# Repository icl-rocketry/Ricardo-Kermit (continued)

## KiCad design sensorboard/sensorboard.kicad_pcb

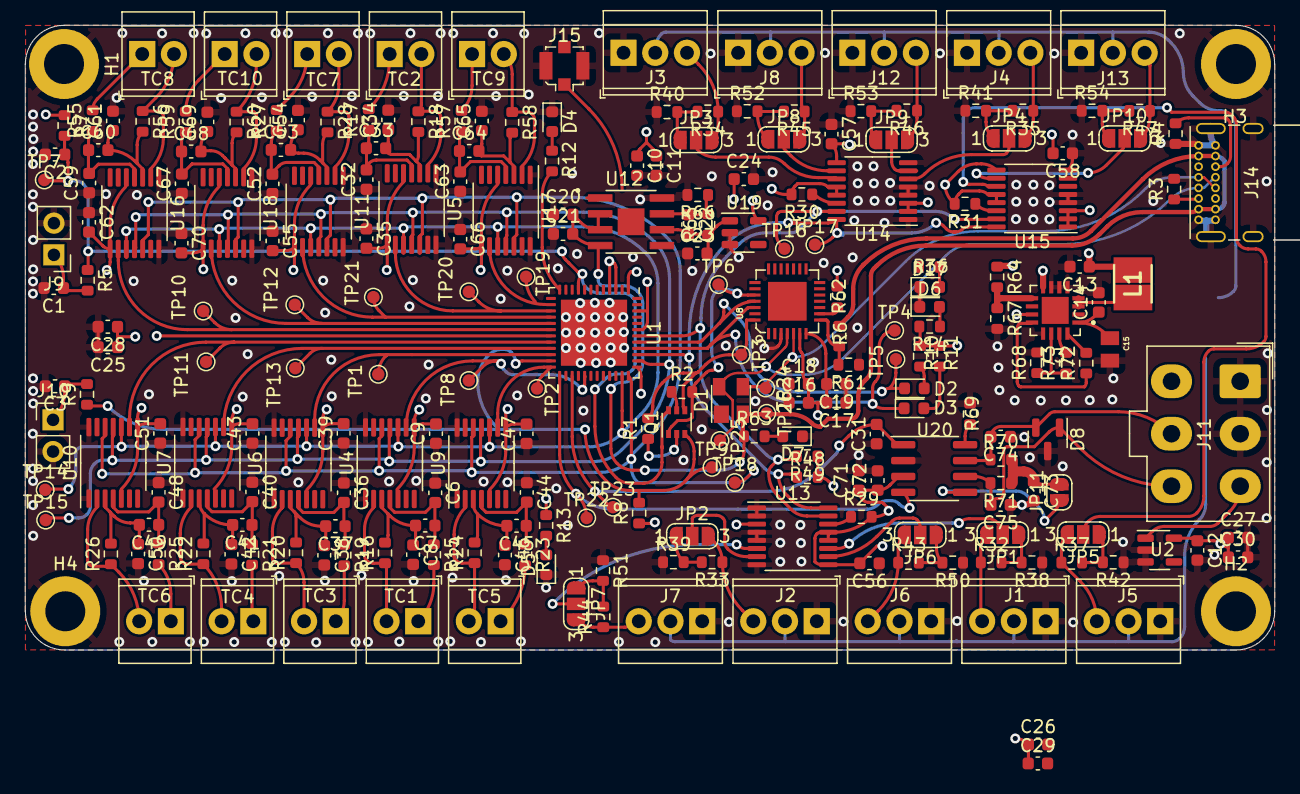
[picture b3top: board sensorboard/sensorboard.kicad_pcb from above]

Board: 4 copper layers, 100.0 x 50.0 mm, 243 parts (0 on the bottom side), 131 nets.

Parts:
C1, C2, C3, C21: 1uF; C_0603_1608Metric
C6, C8, C32, C34, C36, C38, C40, C42, C44, C46, C48, C50, C52, C54, C59, C61, C63, C65, C67, C69: 0.01uF; C_0603_1608Metric
C7, C9, C18, C19, C22, C33, C35, C37, C39, C41, C43, C45, C47, C49, C51, C53, C55, C56, C57, C58, C60, C62, C64, C66, C68, C70, C73: 0.1uF; C_0603_1608Metric
C10, C13, C20, C23, C25, C26, C27, C72: 10uF; C_0603_1608Metric
C11, C28, C29, C30, C71: 100nF; C_0603_1608Metric
C12, C16, C24: 4.7uF; C_0603_1608Metric
C14: 2.2uF; C_0603_1608Metric
C15: 100uF; CAPC2012X145N
C17: 1.0uF; C_0603_1608Metric
C31: 160pF; C_0603_1608Metric
C74: 220pF; C_0603_1608Metric
C75: 220 pF; C_0603_1608Metric
D1: SP0503BAHT; SOT-143
D2: RX_LED; LED_0603_1608Metric
D3: TX_LED; LED_0603_1608Metric
D4, D5: LED; LED_0603_1608Metric
D6: PWR_LED; LED_0603_1608Metric
D7, D17: USB_LED; LED_0603_1608Metric
D8: SM712_SOT23; SOT-23
H1, H2, H3, H4: MountingHole_Pad; MountingHole_3.2mm_M3_DIN965_Pad
J1, J2, J3, J4, J5, J6, J7, J8, J12, J13: Conn_01x03; TerminalBlock_TE_282834-3_1x03_P2.54mm_Horizontal
J9, J10: Conn_01x02_Male; PinHeader_1x02_P2.54mm_Vertical
J11: Conn_01x05_Male; Molex_Mini-Fit_Jr_5566-06A_2x03_P4.20mm_Vertical
J14: USB_C_Receptacle_USB2.0; USB_C_Receptacle_GCT_USB4085
J15: Conn_Coaxial; U.FL_Molex_MCRF_73412-0110_Vertical
JP1, JP2, JP3, JP4, JP5, JP6, JP7, JP8, JP9, JP10: SolderJumper_3_Open; SolderJumper-3_P1.3mm_Open_RoundedPad1.0x1.5mm_NumberLabels
JP11: SolderJumper_2_Open; SolderJumper-2_P1.3mm_Open_RoundedPad1.0x1.5mm
L1: 6.8uH; INDPM3030X200N
Q1: MMDT2222A; SOT-363_SC-70-6
R1, R2, R7, R8: 10K; R_0603_1608Metric
R3, R4: 5.1k; R_0603_1608Metric
R5, R9, R10, R11, R12, R13, R14, R36, R63: 470; R_0603_1608Metric
R6: 24k; R_0603_1608Metric
R15, R16, R17, R18, R19, R20, R21, R22, R23, R24, R25, R26, R27, R28, R55, R56, R57, R58, R59, R60: 100; R_0603_1608Metric
R29, R30, R31, R48, R49: 1k; R_0603_1608Metric
R32, R33, R34, R35, R37, R43, R44, R45, R46, R47: 22k; R_0603_1608Metric
R38, R39, R40, R41, R42, R50, R51, R52, R53, R54: 43k; R_0603_1608Metric
R61: 47k; R_0603_1608Metric
R62: 4.7k; R_0603_1608Metric
R64: 2.184M; R_0603_1608Metric
R65: 56k; R_0603_1608Metric
R66, R69: 10k; R_0603_1608Metric
R67: 390k; R_0603_1608Metric
R68: 200k; R_0603_1608Metric
R70, R71: 60; R_0603_1608Metric
R72: 1M; R_0603_1608Metric
R73: 1.8M; R_0603_1608Metric
TC1, TC2, TC3, TC4, TC5, TC6, TC7, TC8, TC9, TC10: Thermocouple; TerminalBlock_TE_282834-2_1x02_P2.54mm_Horizontal
TP1, TP2, TP3, TP4, TP5, TP6, TP7, TP8, TP9, TP10, TP11, TP12, TP13, TP14, TP15, TP16, TP17, TP18, TP19, TP20, TP21, TP22, TP23, TP24, TP25, TP26: TestPoint; TestPoint_Pad_D1.0mm
U1: ESP32-PICO-D4; QFN-48-1EP_7x7mm_P0.5mm_EP5.3x5.3mm
U2, U19: LTC4411; SOT-23-5
U3: TPS61092RSAR; QFN65P400X400X100-17N
U4, U5, U6, U7, U9, U10, U11, U16, U17, U18: MAX31856; TSSOP-14_4.4x5mm_P0.65mm
U8: CP2102-GMR-QFN28; QFN28G_0.5-5X5MM
U12: SC2416H; SOIC127P599X175-9N
U13, U14, U15: ADS1219; TSSOP-16_4.4x5mm_P0.65mm
U20: SN65HVD230; SOIC-8_3.9x4.9mm_P1.27mm

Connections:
+3V3: C9.2, C10.1, C11.1, C12.1, C13.1, C16.2, C17.2, C18.2, C19.2, C24.1, C25.1, C26.1, C27.1, C28.1, C29.1, C30.1, C35.2, C39.2, C43.2, C47.2, C51.2, C55.2, C56.2, C57.2, C58.2, C62.2, C66.2, C70.2, C71.1, C72.1, L1.1, R7.1, R8.1, R10.1, R11.1, R13.1, R14.2, R29.2, R30.2, R31.2, R48.2, R49.1, R62.1, R64.1, U1.1 (VDDA), U1.3 (VDDA3P3), U1.4 (VDDA3P3), U1.19 (VDD3P3_RTC), U1.37 (VDD3P3_CPU), U1.43 (VDDA), U1.46 (VDDA), U2.5 (OUT), U3.8 (VBAT), U3.11 (EN), U4.5 (AVDD), U4.8 (DVDD), U5.5 (AVDD), U5.8 (DVDD), U6.5 (AVDD), U6.8 (DVDD), U7.5 (AVDD), U7.8 (DVDD), U8.6 (VDD), U8.7 (REGIN), U9.5 (AVDD), U9.8 (DVDD), U10.5 (AVDD), U10.8 (DVDD), U11.5 (AVDD), U11.8 (DVDD), U13.3 (~RESET), U13.9 (REFP), U13.12 (AVDD), U13.13 (DVDD), U14.2 (A1), U14.3 (~RESET), U14.9 (REFP), U14.12 (AVDD), U14.13 (DVDD), U15.1 (A0), U15.2 (A1), U15.3 (~RESET), U15.9 (REFP), U15.12 (AVDD), U15.13 (DVDD), U16.5 (AVDD), U16.8 (DVDD), U17.5 (AVDD), U17.8 (DVDD), U18.5 (AVDD), U18.8 (DVDD), U19.5 (OUT), U20.3 (VCC)
+5V: C14.1, C15.1, J1.2, J2.2, J3.2, J4.2, J5.2, J6.2, J7.2, J8.2, J12.2, J13.2, R72.2, R73.2, U3.1 (VOUT), U3.15 (VOUT), U3.16 (VOUT)
/BOOT: Q1.3 (C2), R8.2, R9.1, TP9.1, U1.23 (IO0)
/CAN/Vref: JP11.1 (A), U20.5 (Vref)
/CAN_HIGH: C74.2, D8.2 (A2), J11.5, R70.1, U20.7 (CANH)
/CAN_LOW: C75.2, D8.1 (A1), J11.6, R71.2, U20.6 (CANL)
/CAN_RX: TP22.1, U1.25 (IO16), U20.4 (R)
/CAN_TX: C31.2, TP23.1, U1.27 (IO17), U20.1 (D)
/CS0: TP8.1, U1.29 (SD3/IO10), U4.9 (~CS)
/CS1: TP20.1, U1.15 (IO26), U5.9 (~CS)
/CS2: TP2.1, U1.24 (IO4), U9.9 (~CS)
/CS3: TP1.1, U1.22 (IO2), U6.9 (~CS)
/CS4: TP13.1, U1.21 (IO15), U7.9 (~CS)
/CS5: TP11.1, U1.20 (IO13), U10.9 (~CS)
/CS6: TP21.1, U1.16 (IO27), U11.9 (~CS)
/CS7: TP10.1, U1.18 (IO12), U16.9 (~CS)
/CS8: TP19.1, U1.14 (IO25), U17.9 (~CS)
/CS9: TP12.1, U1.17 (IO14), U18.9 (~CS)
/DTR: Q1.4 (E2), R1.2, TP3.1, U8.28 (DTR)
/EN: C2.1, Q1.6 (C1), R5.1, R7.2, TP7.1, U1.9 (EN)
/LED: R12.1, U1.12 (IO32)
/LNA_IN: J15.1 (In), U1.2 (LNA_IN)
/MISO: TP15.1, U1.38 (IO19), U4.11 (SDO), U5.11 (SDO), U6.11 (SDO), U7.11 (SDO), U9.11 (SDO), U10.11 (SDO), U11.11 (SDO), U16.11 (SDO), U17.11 (SDO), U18.11 (SDO)
/MOSI: TP18.1, U1.36 (IO23), U4.12 (SDI), U5.12 (SDI), U6.12 (SDI), U7.12 (SDI), U9.12 (SDI), U10.12 (SDI), U11.12 (SDI), U16.12 (SDI), U17.12 (SDI), U18.12 (SDI)
/RTS: Q1.1 (E1), R2.2, TP6.1, U8.24 (RTS)
/RXD: D2.1 (K), TP5.1, U1.41 (U0TXD/IO1), U8.25 (RXD)
/SCL: R48.1, TP17.1, U1.39 (IO22), U13.16 (SCL), U14.16 (SCL), U15.16 (SCL)
/SCLK: TP14.1, U1.35 (IO18), U4.10 (SCK), U5.10 (SCK), U6.10 (SCK), U7.10 (SCK), U9.10 (SCK), U10.10 (SCK), U11.10 (SCK), U16.10 (SCK), U17.10 (SCK), U18.10 (SCK)
/SDA: R49.2, TP16.1, U1.42 (IO21), U13.15 (SDA), U14.15 (SDA), U15.15 (SDA)
/TXD: D3.1 (K), TP4.1, U1.40 (U0RXD/IO3), U8.26 (TXD)
/analogueI2C/AIN0: JP1.2 (C), U13.11 (AIN0)
/analogueI2C/AIN1: JP6.2 (C), U13.10 (AIN1)
/analogueI2C/AIN2: JP2.2 (C), U13.7 (AIN2)
/analogueI2C/AIN3: JP7.2 (C), U13.6 (AIN3)
/analogueI2C/AIN4: JP3.2 (C), U14.11 (AIN0)
/analogueI2C/AIN5: JP8.2 (C), U14.10 (AIN1)
/analogueI2C/AIN6: JP4.2 (C), U14.6 (AIN3)
/analogueI2C/AIN7: JP9.2 (C), U14.7 (AIN2)
/analogueI2C/AIN8: JP5.2 (C), U15.11 (AIN0)
/analogueI2C/AIN9: JP10.2 (C), U15.10 (AIN1)
/usb/Data+: D1.4 (K), J14.A6 (D+), J14.B6 (D+), TP25.1, U8.4 (D+)
/usb/Data-: D1.3 (K), J14.A7 (D-), J14.B7 (D-), TP24.1, U8.5 (D-)
GND: C1.2, C2.2, C3.2, C6.1, C8.2, C9.1, C10.2, C11.2, C12.2, C13.2, C14.2, C15.2, C16.1, C17.1, C18.1, C19.1, C20.1, C21.1, C23.1, C24.2, C25.2, C26.2, C27.2, C28.2, C29.2, C30.2, C31.1, C32.1, C34.2, C35.1, C36.1, C38.2, C39.1, C40.1, C42.2, C43.1, C44.1, C46.2, C47.1, C48.1, C50.2, C51.1, C52.1, C54.2, C55.1, C56.1, C57.1, C58.1, C59.1, C61.2, C62.1, C63.1, C65.2, C66.1, C67.1, C69.2, C70.1, C71.2, C72.2, C73.2, C74.1, C75.1, D1.1 (A), D4.1 (K), D5.1 (K), D6.1 (K), D7.1 (K), D8.3 (common), D17.1 (K), H1.1, H2.1, H3.1, H4.1, J1.1, J2.1, J3.1, J4.1, J5.1, J6.1, J7.1, J8.1, J9.2, J10.2, J11.1, J11.2, J12.1, J13.1, J14.A1 (GND), J14.A12 (GND), J14.B1 (GND), J14.B12 (GND), J14.S1 (SHIELD), J15.2 (Ext), R3.2, R4.1, R38.1, R39.1, R40.1, R41.1, R42.1, R50.1, R51.1, R52.1, R53.1, R54.1, R61.1, R66.2, R67.2, R68.2, R69.2, U1.49 (GND), U2.2 (GND), U2.3 (CTL), U3.5 (PGND), U3.6 (PGND), U3.7 (PGND), U3.10 (SYNC), U3.13 (GND), U3.17 (PGND), U4.1 (AGND), U4.14 (DGND), U5.1 (AGND), U5.14 (DGND), U6.1 (AGND), U6.14 (DGND), U7.1 (AGND), U7.14 (DGND), U8.3 (GND), U9.1 (AGND), U9.14 (DGND), U10.1 (AGND), U10.14 (DGND), U11.1 (AGND), U11.14 (DGND), U12.8 (GND), U13.1 (A0), U13.2 (A1), U13.4 (DGND), U13.5 (AGND), U13.8 (REFN), U14.1 (A0), U14.4 (DGND), U14.5 (AGND), U14.8 (REFN), U15.4 (DGND), U15.5 (AGND), U15.8 (REFN), U16.1 (AGND), U16.14 (DGND), U17.1 (AGND), U17.14 (DGND), U18.1 (AGND), U18.14 (DGND), U19.2 (GND), U19.3 (CTL), U20.2 (GND)
unnamed: C1.1, J9.1, R5.2
unnamed: C3.1, J10.1, R9.2
unnamed: C6.2, C7.1, R15.1, U4.4 (T+)
unnamed: C7.2, C8.1, R16.2, U4.3 (T-)
unnamed: C23.2, R65.1, U12.6 (VOUT), U19.1 (IN)
unnamed: C32.2, C33.1, R17.1, U5.4 (T+)
unnamed: C33.2, C34.1, R18.2, U5.3 (T-)
unnamed: C36.2, C37.1, R19.1, U6.4 (T+)
unnamed: C37.2, C38.1, R20.2, U6.3 (T-)
unnamed: C40.2, C41.1, R21.1, U7.4 (T+)
unnamed: C41.2, C42.1, R22.2, U7.3 (T-)
unnamed: C44.2, C45.1, R23.1, U9.4 (T+)
unnamed: C45.2, C46.1, R24.2, U9.3 (T-)
unnamed: C48.2, C49.1, R25.1, U10.4 (T+)
unnamed: C49.2, C50.1, R26.2, U10.3 (T-)
unnamed: C52.2, C53.1, R27.1, U11.4 (T+)
unnamed: C53.2, C54.1, R28.2, U11.3 (T-)
unnamed: C59.2, C60.1, R55.1, U16.4 (T+)
unnamed: C60.2, C61.1, R56.2, U16.3 (T-)
unnamed: C63.2, C64.1, R57.1, U17.4 (T+)
unnamed: C64.2, C65.1, R58.2, U17.3 (T-)
unnamed: C67.2, C68.1, R59.1, U18.4 (T+)
unnamed: C68.2, C69.1, R60.2, U18.3 (T-)
unnamed: C73.1, JP11.2 (B), R70.2, R71.1
unnamed: D2.2 (A), R10.2
unnamed: D3.2 (A), R11.2
unnamed: D4.2 (A), R12.2
unnamed: D5.2 (A), R13.2
unnamed: D6.2 (A), R14.1
unnamed: D7.2 (A), R63.2
unnamed: D17.2 (A), R36.2
unnamed: J1.3, JP1.3 (B), R32.1
unnamed: J2.3, JP2.3 (B), R33.1
unnamed: J3.3, JP3.3 (B), R34.1
unnamed: J4.3, JP4.3 (B), R35.1
unnamed: J5.3, JP5.3 (B), R37.1
unnamed: J6.3, JP6.3 (B), R43.1
unnamed: J7.3, JP7.3 (B), R44.1
unnamed: J8.3, JP8.3 (B), R45.1
unnamed: J11.3, U2.1 (IN)
unnamed: J12.3, JP9.3 (B), R46.1
unnamed: J13.3, JP10.3 (B), R47.1
unnamed: J14.A5 (CC1), R3.1
unnamed: J14.B5 (CC2), R4.2
unnamed: JP1.1 (A), R32.2, R38.2
unnamed: JP2.1 (A), R33.2, R39.2
unnamed: JP3.1 (A), R34.2, R40.2
unnamed: JP4.1 (A), R35.2, R41.2
unnamed: JP5.1 (A), R37.2, R42.2
unnamed: JP6.1 (A), R43.2, R50.2
unnamed: JP7.1 (A), R44.2, R51.2
unnamed: JP8.1 (A), R45.2, R52.2
unnamed: JP9.1 (A), R46.2, R53.2
unnamed: JP10.1 (A), R47.2, R54.2
unnamed: L1.2, U3.3 (SW), U3.4 (SW)
unnamed: Q1.2 (B1), R1.1
unnamed: Q1.5 (B2), R2.1
unnamed: R6.2, R61.2, U8.8 (VBUS)
unnamed: R15.2, TC1.1 (+)
unnamed: R16.1, TC1.2 (-), U4.2 (BIAS)
unnamed: R17.2, TC2.1 (+)
unnamed: R18.1, TC2.2 (-), U5.2 (BIAS)
unnamed: R19.2, TC3.1 (+)
unnamed: R20.1, TC3.2 (-), U6.2 (BIAS)
unnamed: R21.2, TC4.1 (+)
unnamed: R22.1, TC4.2 (-), U7.2 (BIAS)
unnamed: R23.2, TC5.1 (+)
unnamed: R24.1, TC5.2 (-), U9.2 (BIAS)
unnamed: R25.2, TC6.1 (+)
unnamed: R26.1, TC6.2 (-), U10.2 (BIAS)
unnamed: R27.2, TC7.1 (+)
unnamed: R28.1, TC7.2 (-), U11.2 (BIAS)
unnamed: R29.1, U13.14 (~DRDY)
unnamed: R30.1, U14.14 (~DRDY)
unnamed: R31.1, U15.14 (~DRDY)
unnamed: R55.2, TC8.1 (+)
unnamed: R56.1, TC8.2 (-), U16.2 (BIAS)
unnamed: R57.2, TC9.1 (+)
unnamed: R58.1, TC9.2 (-), U17.2 (BIAS)
unnamed: R59.2, TC10.1 (+)
unnamed: R60.1, TC10.2 (-), U18.2 (BIAS)
unnamed: R62.2, U8.9 (~RST)
unnamed: R64.2, R67.1, U3.9 (LBI)
unnamed: R65.2, R66.1, U12.7 (ADJ)
unnamed: R68.1, R73.1, U3.14 (FB)
unnamed: R69.1, U20.8 (Rs)
unnamed: R72.1, U3.12 (LBO)
VBUS: C20.2, C21.2, D1.2 (K), J14.A4 (VBUS), J14.A9 (VBUS), J14.B4 (VBUS), J14.B9 (VBUS), R6.1, R63.1, TP26.1, U12.2 (EN), U12.3 (VIN)

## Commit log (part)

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2021-11-08 Initial sensor board schematic
    Laid out initial sensor board schematic for up to 12 ch inputs with 250Hz max sampling rate (at maximum oversampling rate of 16384) on continuous sampling mode
2021-11-09 Voltage divider setup
    Voltage divider setup, removed unused components, CAN RX/TX empty for now (waiting for kiran)
2021-11-09 Minor edits
    descriptors
2021-11-13 I2C ADC conversion+MCP31856 x10
    As above xD
    just need to do the pcb layout
2021-11-24 Antenna
2021-12-04 Small edits
    removed a floating extra antenna
2022-03-29 added 5v boost to schematic, should be ready for layout
2022-03-29 schemtiac update
2022-04-05 usb-uart structure done
    Original FPs were used, copies from usb were deleted, however the structure was kept the same
2022-04-13 CAN structure done
    Main structure copied across from actuator board, fps from sensor board used
2022-04-15 antenna and thermocouple prelim
    Preliminary layout for thermocouples and antenna structure done
2022-04-16 Changed diode fps from castellated
2022-05-21 Thermocouple structures
2022-05-31 Update thermocouple connection
    changed schematic (c55 --> cs5) and positions. Copies made
2022-06-03 thermocouple tps and connection update
2022-06-07 Integrated in USB and CAN
    CAN_TX and CAN_RX are moved
2022-06-07 3.3V connections and I2C capacitors
2022-06-11 moved the U14 component and added component
2022-06-18 transistor integration
2022-06-18 connectors and changed capacitor values
    capacitors for the connectors to 0.1uf
2022-06-18 rearrange CAN, USB port and new copies
2022-06-25 LEDs and repositioning for 5V
2022-06-27 Decoupling capacitors
2022-06-27 Initial GND fill and fixed CAN_HIGH
2022-07-02 fills and connecting islands
2022-07-03 Swapped the antenna for the coaxial connector
2022-07-13 USB moved, changed layer ln.2 to 3.3V
    Fixed the GND fill
2022-07-13 Change 3.3V, added curved edges
    changed the copy, added keepout for UFL connector
2022-07-13 changed BOOT pin, auto reset caps
    moved references about
2022-07-24 rearranged CAN and boost converter
    LEDs moved
2022-07-24 fixed clearance issues
    clearance set to 0.21mm
2022-07-26 boost converter fixed
    rearrangement of coaxial connector line and gnd stitching
2022-07-27 Changed pins for CAN lines and removed LED
    need to rearrange LNA_IN line for less interference
2022-07-27 added silkscreens and fixed LNA_IN line
    fixed labels for TPs and LEDs
2022-07-28 Solder jumper silkscreens and moved MOSI
2022-07-30 fixed CS lines
    before cleanup
2022-08-04 Connected LDO and CP2102 EPs to GND, expanded U.FL keepout
2022-08-12 folder structure, added ADS1219 code
2022-08-18 Changed default conversion mode from single-shot to continuous
2022-09-01 Added pin defs, shamelessly stolen .ini and partition files
    also moved ADS class and added the code I used to test 1 ADC channel
2022-09-05 Added config file, copied Ricardo_OS
2022-09-06 added submodules, deleted unnecessaryRic-OS files
2022-09-09 Copied ric-gateway,added getOffset and readAdjusted methods to ADS class
2022-09-18 offset calibration code fixed, found offsets for 1 of the sensor boards
2022-09-18 forgot to commit these
2022-09-19 fixed the ADS class
2022-09-23 Added NTC Thermistor class, tweaks to ADS class
2022-09-24 added pressure transducer class, explicitly cast all integers by length
2022-10-01 copied Kiran's e-match netconf, unfinished loadcell code
2022-10-05 Finished (maybe) loadcell class
2022-10-06 Added a telemetry command and a struct for analong sensors
    command numbers and stuff needs changing to integrate with the rest of the network
2022-10-07 changed telemetry command
2022-10-08 andrei use initializer lists
2022-10-08 updated librnp & rrc, fixed loadcell class
2022-10-08 Changed thermistor and ptap classes to use references instead of ptr
2022-10-08 added command to return raw adc readings
2022-10-08 Updated ADS class to use enums for data rates
2022-10-09 Defined random code numbers as static constexpr
2022-10-14 fixed ptaps and thermistor, load cell needs calibration
2022-10-21 EUROC fixes (I don't remember what I changed)
2022-11-05 Add pickle SD card + delete copies
    need to finish IO
2022-11-05 SD hierarchical labels
    need to connect to new GPIO for esp32-s3
2022-11-08 integrated new ESP32-s3
    Need to remove excess thermocouples
2022-11-08 removed thermocouples
    updated connections
2022-11-19 connectors and update
2022-11-22 potential divider preliminary
    for connectors
2022-12-06 values for ADC caps and connector circuits
    ADC cap values based on assumptions
2022-12-06 fixed hierarchical labels and added ref values
2022-12-10 added 10V rail, moved to boosts sheet
2022-12-13 update
    still need to fix 10v rail
2023-01-21 update 10v rail
2023-01-24 added template changes
    Moved power to seperate file
2023-01-28 grouping layout
2023-01-31 nanofit placements
2023-02-04 added low pass filters for ADC inputs
2023-02-04 update before power layout
2023-02-04 power layout done
2023-02-07 update (tps and filters)
2023-02-11 redimensioning to 120x50mm
    also finished tps
2023-02-21 10v rail layout, adc update
2023-02-21 ADC update
2023-02-25 esp32 pin rearrangement
2023-02-28 esp32-s3 placement
2023-02-28 ADC SPI connections
2023-03-04 ADC connections and KiCAD version update
2023-03-04 added LEDS and CAN connections
2023-03-11 changed pins layout for esp
    update for ADC traces
2023-03-11 traces for CAN and SD card done
2023-03-14 added values for the 10V option
2023-03-18 Powerlines and LDO layout
    updated fp for usb
2023-03-18 fix usb lines
2023-03-25 GND and 3.3v planes
2023-03-25 fixed planes and added tps
2023-03-25 Deleted thermal relief on mounting
2023-03-25 update
    not sure, forgot to save
2023-04-01 started writing zeroing stuff, pre-Romania commit
2023-04-01 Auto stash before merge of "main" and "origin/main"
2023-04-22 Added thermocouple support
2023-05-15 TCs work but max31856 class needs some tweaks
2023-05-16 slight changes to TC driver, will probably revert some of them
2023-05-23 changes to schematic
    added in components for the layout
2023-05-27 changing power layout and thermocouples
2023-05-30 Power sorted
2023-05-30 changed SPI layout
2023-06-02 changed thickness of traces
    VBUS and RBUS
2023-06-03 fixed the CAN
2023-06-04 ADS line fix and schematic
2023-06-10 differential running and fixed ADS schematic
2023-06-10 Silkscreen for all fps and back plate
2023-06-10 JTAG tps fixed and teardrops
2023-06-13 termination resistor and DRC cleanup
2023-06-17 idk what this is
2023-06-18 switched tc references
2023-06-19 cleanup
2023-06-27 edge clearance
2023-06-28 Dynamic zero + calibration for loadcell, NVS started but needs changing
    I forgot to push last time which messed up git
2023-07-05 new boosts schem and layout
2023-07-06 fixed spi lines
2023-07-07 rerouted USB D traces, redid ADSCLK and source termination, some...
    ... other small things too.
2023-07-07 drc relay
2023-07-08 left hand side mostly cleaned up
2023-07-08 silkscreen cleaning
2023-07-08 inshallah
2023-07-13 ordering changes
2023-08-11 started firmware
2023-08-11 Actually adding firmware this time...
2023-08-14 added ADS drivers (incomplete)
    starting implementation and some documentation. need to fix stuff
2023-08-14 Pinmap and ADC implementation update
    need to sort out ledc
2023-08-19 Fixed submodules
2023-08-19 Forgot arduinojson
2023-08-24 updated ADS drivers (requires testing)
    twocompdecomp requires fixing. testing required. pushing changes before stuff is messed up
2023-08-26 changed c style arrays to vects and fixed compile errors
2023-08-26 Initialised SPI and started on nrc components
2023-08-30 moved sensors from librrc, set up sensor objects, raw ADC reading packet&command
2023-08-30 pulled libriccore for serial fix
2023-09-02 set up CAN interface
2023-09-05 Implemented ptap calibration
2023-09-12 idfk man
2023-09-17 rolled back to before merge, reimplemented some things
2023-09-18 tryna fix the crashing
2023-09-25 fixed some bugs. updated libriccore to latest, redirected syslogger to librricore implmenetation, decreased log delta
2023-09-27 updated file opening to correct oflags
2023-09-28 updated comopnents to latest main
2023-09-28 changed osr
2023-10-02 updated to latest libricore and librnp
2023-11-04 Added Hello to license
2023-11-28 Start of Kermit Mini
2023-12-05 Power supply pins
2023-12-08 speeding up sd card
2024-01-23 Revert "Merge remote-tracking branch 'refs/remotes/origin/main'"
    This reverts commit c9a99cb72454eddb78504ad976151236a8d13e5c, reversing
    changes made to 3cdb2e540a9938f01cf78ecb1078cc5742e66bb5.
2024-02-06 small fix
2024-02-06 and forgot to comment out some old TC code
2024-02-08 tc update delta, fixed flow sensor k
2024-02-08 updated libricore
2024-02-08 forgot to update the time in the max31856 class ...
2024-02-08 Changed back to shared spi mode so sd cards unshits itself
2024-02-28 flow sensor integration and somewhat better sd card logging
2024-03-07 Flow Sensor integration with new PCNT code structure
2024-03-12 Kermit Mini
2024-03-12 wowwww
2024-03-16 added get error method to sdfat_store
2024-03-17 .ini change for SD card fixes
2024-03-22 Changed TC CJ behaviour so that TCs nominal read time is 57 ms
2024-03-22 Removed original sdfat, moving to fork
2024-03-22 Re-integrated flow sensor
2024-04-09 fixed sd card error flag
2024-04-20 Added fault checking and an alive method to the MAX31856
2024-05-20 Start work
2024-05-28 not sure what changed
2024-05-28 random log file
2024-05-29 added redline monitoring
2024-06-09 Added Kermit Mini Board
2024-06-09 Actually added Kermit Mini
2024-07-10 Rewritten to support individual valve actions
2024-07-15 modified redline calibration
2024-07-16 wrapping up layout
2024-07-16 layout
2024-07-22 added diodes on gpio breakout and sensor supply
2024-07-22 Cosmos tweaks for readline
2024-07-28 changed ldo output to 12v, kiran review done
2024-07-30 hope shiven is happy
2024-07-30 changed boost output cap to 0603
2024-08-05 changes post 3rd review
2024-08-05 changed R23 to match stark
2024-08-12 post Andrei review, new SD
2024-08-13 again
2024-08-15 p mosfet pinout fix
2024-08-16 changed sd det pinout
2024-08-16 Ordering
2024-09-05 linker error
2024-09-05 ADS131M04 reading 4 channels
2024-09-12 Added 3d Components
2024-09-23 hopefully merging with 3d model changes
2024-09-23 got rid of rando hardware files and irrelevant error flags
2024-10-04 pulled in some logging changes
2024-10-04 submodule updates
2024-12-12 Moved kermit mini firmware to its own firmware folder
2024-12-12 Moved v2(board iteration) firmware to its own folder
2024-12-12 ignore ds store
2024-12-12 fixed gitmodules for the folder split. Having the different hardware's firmware in different folders isn't ideal, and will be fixed for v4
2024-12-12 USB and power schematics died in the merge
2025-01-08 Fixed merge conflict
2025-01-08 Esp-idf doesn't like brackets in folder name + more merge fixes
2025-01-08 v2 firmware fixed too.
2025-01-13 updated espressif32 platform version to latest
2025-01-13 correct submodule versions for idf5.3
2025-01-13 Changed ADS131M04 class to updated LEDC API
2025-01-13 Copied over partition and sdk settings from template
2025-02-12 Started dynamic sensors again after 2 years
2025-02-15 Variant-related functionality mostly implemented, can't change held value yet
2025-02-17 Sensors replaced with adc channel classes. NOTE: Full functionality is not yet implemented.
2025-02-17 Switched to tracking packet types in RNP
2025-04-23 changed raw adc packet to int32
2025-04-23 reset on initialising ADS131M04 and fast millis in MAX31856 loop
2025-04-23 Replaced micros call with esp timer
2025-04-23 More appropriate OSR for effective sampling rate (470 SPS)
2025-04-23 Added file header at the start of telemetry log and changed to .csv
2025-05-16 Fix - having c++ exceptions disabled causes restart on any exception, including caught ones
2025-05-16 update submodule commits
2025-05-16 Rolled back arduino due to compile errors
2025-12-27 v4 submodules
2026-04-23 currently in the basket
2026-04-23 removed lck and backups from git
2026-06-20 Swapped v3 and v2 to improve readability in README.md
2026-06-24 tidy up schematic and bom
2026-06-24 continued
2026-06-27 Display ADC readings on SPI OLED.
2026-06-28 Made the display nicer.
